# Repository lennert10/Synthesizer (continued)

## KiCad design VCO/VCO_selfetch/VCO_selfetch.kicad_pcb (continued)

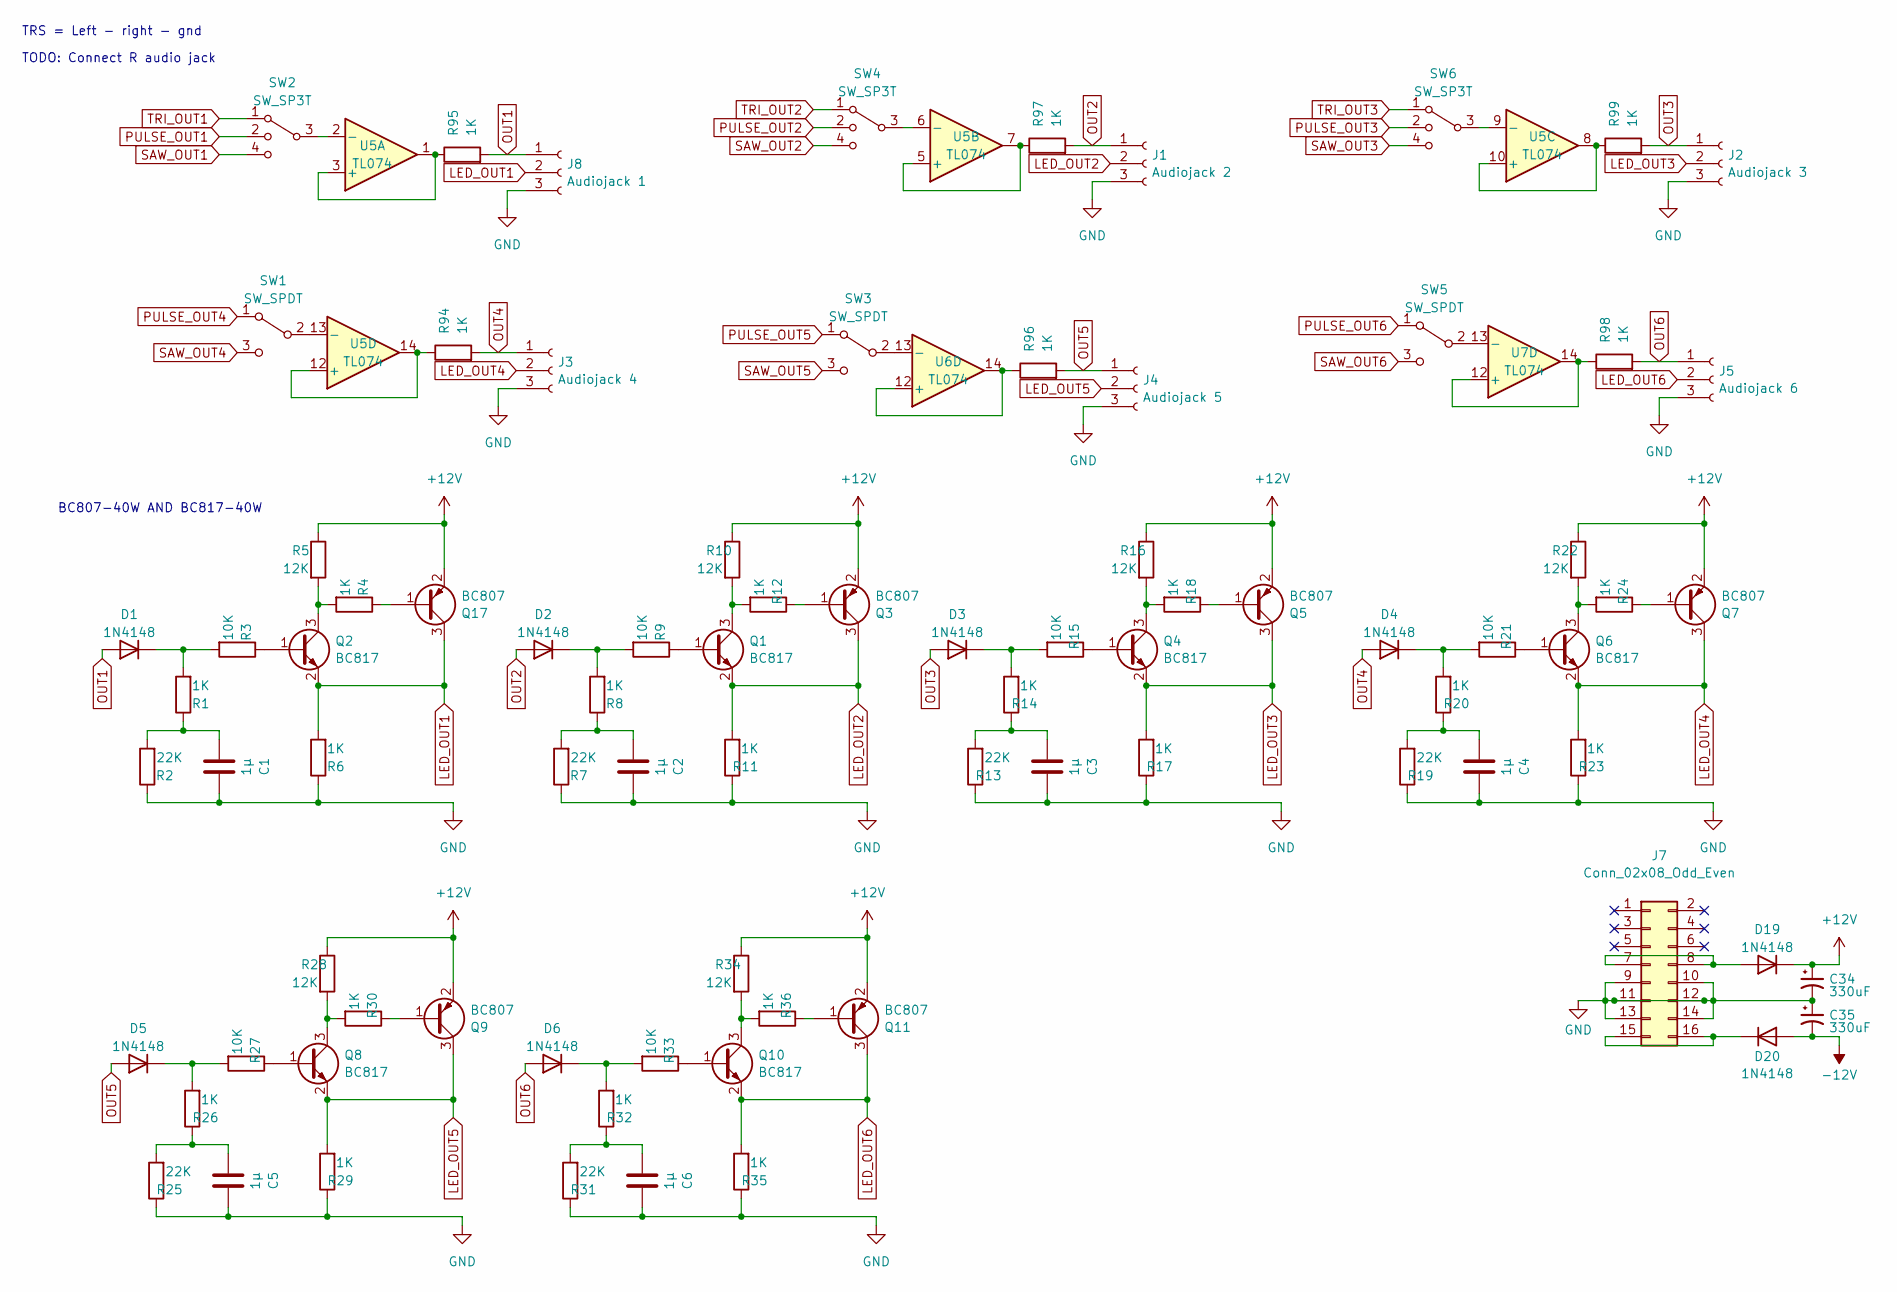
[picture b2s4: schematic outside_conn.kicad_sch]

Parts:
C1, C2, C3, C4, C5, C6: 1µ; C_0402_1005Metric_Pad0.74x0.62mm_HandSolder
C34, C35: 330uF; CP_Radial_D12.5mm_P7.50mm
D1, D2, D3, D4, D5, D6, D19, D20: 1N4148; D_SOD-123
J1: Audiojack 2; PinHeader_1x03_P2.54mm_Vertical
J2: Audiojack 3; PinHeader_1x03_P2.54mm_Vertical
J3: Audiojack 4; PinHeader_1x03_P2.54mm_Vertical
J4: Audiojack 5; PinHeader_1x03_P2.54mm_Vertical
J5: Audiojack 6; PinHeader_1x03_P2.54mm_Vertical
J7: Conn_02x08_Odd_Even; PinHeader_2x08_P2.54mm_Vertical
J8: Audiojack 1; PinHeader_1x03_P2.54mm_Vertical
Q1, Q2, Q4, Q6, Q8, Q10: BC817; SOT-23
Q3, Q5, Q7, Q9, Q11, Q17: BC807; SOT-23
R1, R4, R6, R8, R11, R12, R14, R17, R18, R20, R23, R24, R26, R29, R30, R32, R35, R36, R94, R95, R96, R97, R98, R99: 1K; R_0603_1608Metric_Pad0.98x0.95mm_HandSolder
R2, R7, R13, R19, R25, R31: 22K; R_0603_1608Metric_Pad0.98x0.95mm_HandSolder
R3, R9, R15, R21, R27, R33: 10K; R_0603_1608Metric_Pad0.98x0.95mm_HandSolder
R5, R10, R16, R22, R28, R34: 12K; R_0603_1608Metric_Pad0.98x0.95mm_HandSolder
SW1, SW3, SW5: SW_SPDT; PinHeader_1x03_P2.54mm_Vertical
SW2, SW4, SW6: SW_SP3T; PinHeader_1x04_P2.54mm_Vertical
U5, U6, U7: TL074; DIP-14_W7.62mm_Socket

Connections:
+12V: C34.1, D19.1 (K), Q3.2 (E), Q5.2 (E), Q7.2 (E), Q9.2 (E), Q11.2 (E), Q17.2 (E), R5.1, R10.1, R16.1, R22.1, R28.1, R34.1; also elsewhere on the board
-12V: C35.2, D20.2 (A); also elsewhere on the board
GND: C1.1, C2.1, C3.1, C4.1, C5.1, C6.1, C34.2, C35.1, J1.3, J2.3, J3.3, J4.3, J5.3, J7.9, J7.10, J7.11, J7.12, J7.13, J7.14, J8.3, R2.1, R6.1, R7.1, R11.1, R13.1, R17.1, R19.1, R23.1, R25.1, R29.1, R31.1, R35.1; also elsewhere on the board
LED_OUT1: J8.2, Q2.2 (E), Q17.3 (C), R6.2
LED_OUT2: J1.2, Q1.2 (E), Q3.3 (C), R11.2
LED_OUT3: J2.2, Q4.2 (E), Q5.3 (C), R17.2
LED_OUT4: J3.2, Q6.2 (E), Q7.3 (C), R23.2
LED_OUT5: J4.2, Q8.2 (E), Q9.3 (C), R29.2
LED_OUT6: J5.2, Q10.2 (E), Q11.3 (C), R35.2
unnamed: C1.2, R1.1, R2.2
unnamed: C2.2, R7.2, R8.1
unnamed: C3.2, R13.2, R14.1
unnamed: C4.2, R19.2, R20.1
unnamed: C5.2, R25.2, R26.1
unnamed: C6.2, R31.2, R32.1
unnamed: D1.1 (K), R1.2, R3.2
unnamed: D2.1 (K), R8.2, R9.2
unnamed: D3.1 (K), R14.2, R15.2
unnamed: D4.1 (K), R20.2, R21.2
unnamed: D5.1 (K), R26.2, R27.2
unnamed: D6.1 (K), R32.2, R33.2
unnamed: D19.2 (A), J7.7, J7.8
unnamed: D20.1 (K), J7.15, J7.16
unnamed: Q1.1 (B), R9.1
unnamed: Q1.3 (C), R10.2, R12.2
unnamed: Q2.1 (B), R3.1
unnamed: Q2.3 (C), R4.2, R5.2
unnamed: Q3.1 (B), R12.1
unnamed: Q4.1 (B), R15.1
unnamed: Q4.3 (C), R16.2, R18.2
unnamed: Q5.1 (B), R18.1
unnamed: Q6.1 (B), R21.1
unnamed: Q6.3 (C), R22.2, R24.2
unnamed: Q7.1 (B), R24.1
unnamed: Q8.1 (B), R27.1
unnamed: Q8.3 (C), R28.2, R30.2
unnamed: Q9.1 (B), R30.1
unnamed: Q10.1 (B), R33.1
unnamed: Q10.3 (C), R34.2, R36.2
unnamed: Q11.1 (B), R36.1
unnamed: Q17.1 (B), R4.1
unnamed: SW1.2 (B), U5.13 (-)
unnamed: SW3.2 (B), U6.13 (-)
unnamed: SW5.2 (B), U7.13 (-)
unnamed: R95.1, U5.1, U5.3 (+)
unnamed: SW2.3, U5.2 (-)
unnamed: R97.1, U5.5 (+), U5.7
unnamed: SW4.3, U5.6 (-)
unnamed: R99.1, U5.8, U5.10 (+)
unnamed: SW6.3, U5.9 (-)
unnamed: R94.1, U5.12 (+), U5.14
unnamed: R96.1, U6.12 (+), U6.14
unnamed: R98.1, U7.12 (+), U7.14
OUT1: D1.2 (A), J8.1, R95.2
OUT2: D2.2 (A), J1.1, R97.2
OUT3: D3.2 (A), J2.1, R99.2
OUT4: D4.2 (A), J3.1, R94.2
OUT5: D5.2 (A), J4.1, R96.2
OUT6: D6.2 (A), J5.1, R98.2
PULSE_OUT1: SW2.2; also elsewhere on the board
PULSE_OUT2: SW4.2; also elsewhere on the board
PULSE_OUT3: SW6.2; also elsewhere on the board
PULSE_OUT4: SW1.1 (A); also elsewhere on the board
PULSE_OUT5: SW3.1 (A); also elsewhere on the board
PULSE_OUT6: SW5.1 (A); also elsewhere on the board
SAW_OUT1: SW2.4; also elsewhere on the board
SAW_OUT2: SW4.4; also elsewhere on the board
SAW_OUT3: SW6.4; also elsewhere on the board
SAW_OUT4: SW1.3 (C); also elsewhere on the board
SAW_OUT5: SW3.3 (C); also elsewhere on the board
SAW_OUT6: SW5.3 (C); also elsewhere on the board
TRI_OUT1: SW2.1; also elsewhere on the board
TRI_OUT2: SW4.1; also elsewhere on the board
TRI_OUT3: SW6.1; also elsewhere on the board

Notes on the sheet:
TRS = Left - right - gnd
BC807-40W AND BC817-40W
TODO: Connect R audio jack

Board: 4 copper layers, 307 parts (0 on the bottom side), 209 nets, no tracks yet.

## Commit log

2023-01-23 first VCO added
2023-01-27 small fixes
2023-02-11 changes vco
2023-02-24 added vco 2 and 3
2023-03-07 simple vco's added
2024-10-21 continue
2024-10-30 footprint WIP
2024-10-30 all save
2024-10-30 single version added
2024-11-04 61354534648
2024-11-04 pcb v0.9
